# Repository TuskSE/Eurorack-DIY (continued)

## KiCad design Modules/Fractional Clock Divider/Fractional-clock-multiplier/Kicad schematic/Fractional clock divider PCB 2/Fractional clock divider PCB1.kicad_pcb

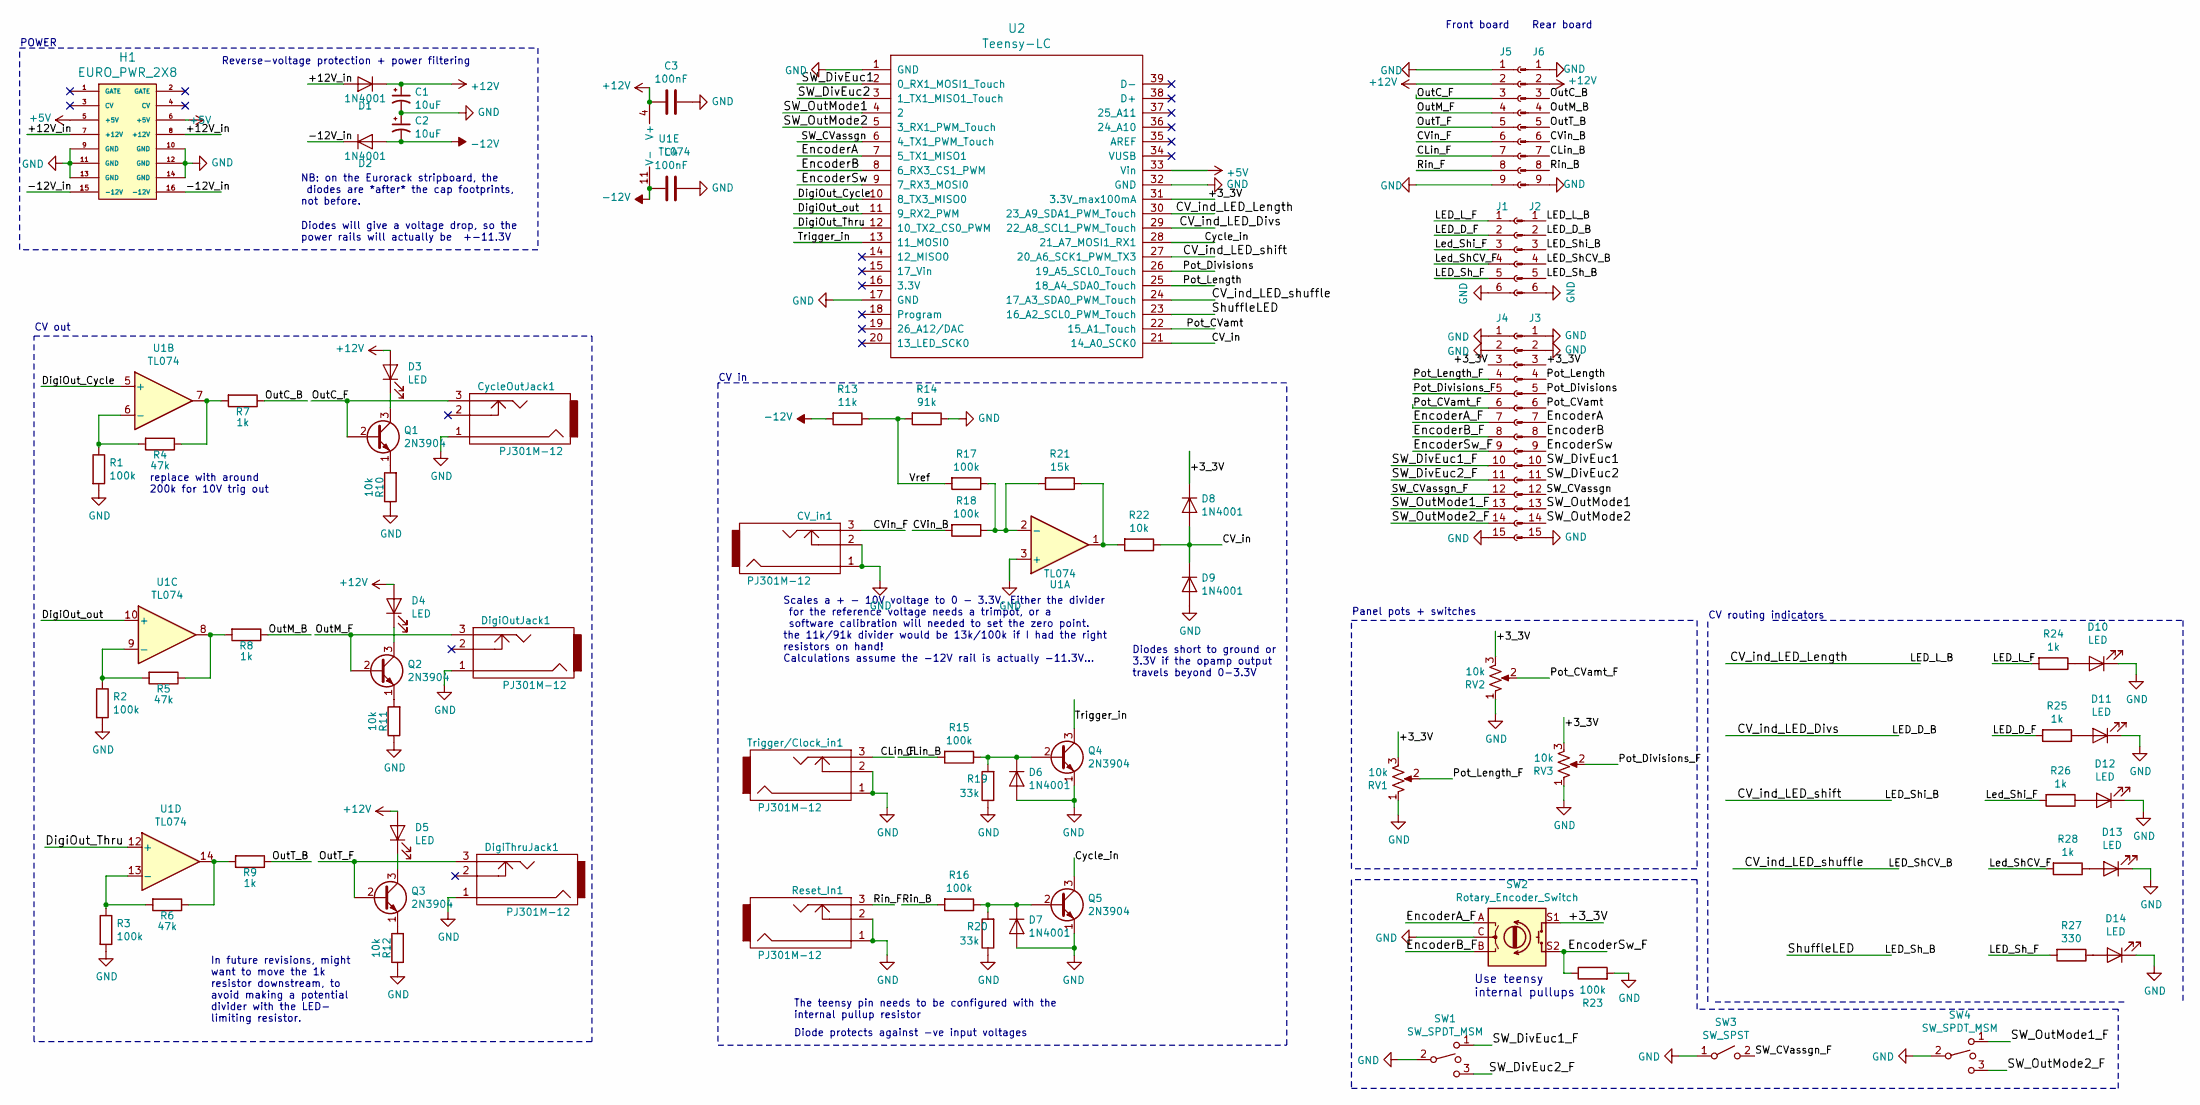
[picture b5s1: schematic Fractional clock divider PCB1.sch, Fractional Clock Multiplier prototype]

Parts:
C1, C2: 10uF; CP_Radial_D5.0mm_P2.00mm
C3, C4: 100nF; C_Rect_L11.5mm_W4.0mm_P10.00mm_MKT
CV_in1: PJ301M-12
CycleOutJack1: PJ301M-12
D1, D2, D6, D7, D8, D9: 1N4001; D_DO-41_SOD81_P10.16mm_Horizontal
D3, D4, D5, D10, D11, D12, D13, D14: LED; LED_D3.0mm
DigiOutJack1: PJ301M-12
DigiThruJack1: PJ301M-12
H1: EURO_PWR_2X8; PinSocket_2x08_P2.54mm_Vertical
J1: Conn_01x06_Female; PinHeader_1x06_P2.54mm_Vertical
J2: Conn_01x06_Male; PinHeader_1x06_P2.54mm_Vertical
J3: Conn_01x15_Male; PinHeader_1x15_P2.54mm_Vertical
J4: Conn_01x15_Female; PinHeader_1x15_P2.54mm_Vertical
J5: Conn_01x09_Female; PinHeader_1x09_P2.54mm_Vertical
J6: Conn_01x09_Male; PinHeader_1x09_P2.54mm_Vertical
Q1, Q2, Q3, Q4, Q5: 2N3904; TO-92_Inline
R1, R2, R3, R15, R16, R17, R18, R23: 100k; R_Axial_DIN0207_L6.3mm_D2.5mm_P10.16mm_Horizontal
R4, R5, R6: 47k; R_Axial_DIN0207_L6.3mm_D2.5mm_P10.16mm_Horizontal
R7, R8, R9, R24, R25, R26, R28: 1k; R_Axial_DIN0207_L6.3mm_D2.5mm_P10.16mm_Horizontal
R10, R11, R12, R22: 10k; R_Axial_DIN0207_L6.3mm_D2.5mm_P10.16mm_Horizontal
R13: 11k; R_Axial_DIN0207_L6.3mm_D2.5mm_P10.16mm_Horizontal
R14: 91k; R_Axial_DIN0207_L6.3mm_D2.5mm_P10.16mm_Horizontal
R19, R20: 33k; R_Axial_DIN0207_L6.3mm_D2.5mm_P10.16mm_Horizontal
R21: 15k; R_Axial_DIN0207_L6.3mm_D2.5mm_P10.16mm_Horizontal
R27: 330; R_Axial_DIN0207_L6.3mm_D2.5mm_P10.16mm_Horizontal
RV1, RV2, RV3: 10k; Alpha9mmPot
Reset_In1: PJ301M-12
SW1, SW4: SW_SPDT_MSM; SPDT toggle on-off-on
SW2: Rotary_Encoder_Switch; RotaryEncoder_Alps_EC11E-Switch_Vertical_H20mm_CircularMoun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
SW3: SW_SPST; SPST momentary push PBS105
Trigger/Clock_in1: PJ301M-12
U1: TL074; DIP-14_W7.62mm_LongPads
U2: Teensy-LC; TeensyLC_fixed_pads

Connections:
+5V: H1.5 (+5V), H1.6 (+5V), U2.33 (Vin)
+12V: C1.1, C3.2, D1.1 (K), D3.2 (A), D4.2 (A), D5.2 (A), J5.2, J6.2, U1.4 (V+)
-12V: C2.2, C4.1, D2.2 (A), R13.2, U1.11 (V-)
/+3_3V: D8.1 (K), J3.3, J4.3, RV1.3, RV2.3, RV3.3, SW2.S1, U2.31 (3.3V_max100mA)
/+12V_in: D1.2 (A), H1.7 (+12V), H1.8 (+12V)
/-12V_in: D2.1 (K), H1.15 (-12V), H1.16 (-12V)
/CLin_B: J6.7, R15.2
/CLin_F: J5.7, Trigger/Clock_in1.3
/CV_in: D8.2 (A), D9.1 (K), R22.1, U2.21 (14_A0_SCK0)
/CV_ind_LED_Divs: J2.2, U2.29 (22_A8_SCL1_PWM_Touch)
/CV_ind_LED_Length: J2.1, U2.30 (23_A9_SDA1_PWM_Touch)
/CV_ind_LED_shift: J2.3, U2.27 (20_A6_SCK1_PWM_TX3)
/CV_ind_LED_shuffle: J2.4, U2.24 (17_A3_SDA0_PWM_Touch)
/CVin_B: J6.6, R18.2
/CVin_F: CV_in1.3, J5.6
/Cycle_in: Q5.3 (C), U2.28 (21_A7_MOSI1_RX1)
/DigiOut_Cycle: U1.5 (+), U2.10 (8_TX3_MISO0)
/DigiOut_Thru: U1.12 (+), U2.12 (10_TX2_CS0_PWM)
/DigiOut_out: U1.10 (+), U2.11 (9_RX2_PWM)
/EncoderA: J3.7, U2.7 (5_TX1_MISO1)
/EncoderA_F: J4.7, SW2.A
/EncoderB: J3.8, U2.8 (6_RX3_CS1_PWM)
/EncoderB_F: J4.8, SW2.B
/EncoderSw: J3.9, U2.9 (7_RX3_MOSI0)
/EncoderSw_F: J4.9, R23.1, SW2.S2
/LED_D_F: J1.2, R25.2
/LED_L_F: J1.1, R24.2
/LED_Sh_B: J2.5, U2.23 (16_A2_SCL0_PWM_Touch)
/LED_Sh_F: J1.5, R27.2
/Led_ShCV_F: J1.4, R28.2
/Led_Shi_F: J1.3, R26.2
/OutC_B: J6.3, R7.1
/OutC_F: CycleOutJack1.3, J5.3, Q1.2 (B)
/OutM_B: J6.4, R8.1
/OutM_F: DigiOutJack1.3, J5.4, Q2.2 (B)
/OutT_B: J6.5, R9.1
/OutT_F: DigiThruJack1.3, J5.5, Q3.2 (B)
/Pot_CVamt: J3.6, U2.22 (15_A1_Touch)
/Pot_CVamt_F: J4.6, RV2.2
/Pot_Divisions: J3.5, U2.26 (19_A5_SCL0_Touch)
/Pot_Divisions_F: J4.5, RV3.2
/Pot_Length: J3.4, U2.25 (18_A4_SDA0_Touch)
/Pot_Length_F: J4.4, RV1.2
/Rin_B: J6.8, R16.2
/Rin_F: J5.8, Reset_In1.3
/SW_CVassgn: J3.12, U2.6 (4_TX1_PWM_Touch)
/SW_CVassgn_F: J4.12, SW3.2 (B)
/SW_DivEuc1: J3.10, U2.2 (0_RX1_MOSI1_Touch)
/SW_DivEuc1_F: J4.10, SW1.1
/SW_DivEuc2: J3.11, U2.3 (1_TX1_MISO1_Touch)
/SW_DivEuc2_F: J4.11, SW1.3
/SW_OutMode1: J3.13, U2.4 (2)
/SW_OutMode1_F: J4.13, SW4.1
/SW_OutMode2: J3.14, U2.5 (3_RX1_PWM_Touch)
/SW_OutMode2_F: J4.14, SW4.3
/Trigger_in: Q4.3 (C), U2.13 (11_MOSI0)
/Vref: R13.1, R14.2, R17.2
GND: C1.2, C2.1, C3.1, C4.2, CV_in1.1, CV_in1.2, CycleOutJack1.1, D6.2 (A), D7.2 (A), D9.2 (A), D10.1 (K), D11.1 (K), D12.1 (K), D13.1 (K), D14.1 (K), DigiOutJack1.1, DigiThruJack1.1, H1.9 (GND), H1.10 (GND), H1.11 (GND), H1.12 (GND), H1.13 (GND), H1.14 (GND), J1.6, J2.6, J3.1, J3.2, J3.15, J4.1, J4.2, J4.15, J5.1, J5.9, J6.1, J6.9, Q4.1 (E), Q5.1 (E), R1.2, R2.2, R3.2, R10.1, R11.1, R12.1, R14.1, R19.1, R20.1, R23.2, RV1.1, RV2.1, RV3.1, Reset_In1.1, Reset_In1.2, SW1.2, SW2.C, SW3.1 (A), SW4.2, Trigger/Clock_in1.1, Trigger/Clock_in1.2, U1.3 (+), U2.1 (GND), U2.17 (GND), U2.32 (GND)
unnamed: D3.1 (K), Q1.3 (C)
unnamed: D4.1 (K), Q2.3 (C)
unnamed: D5.1 (K), Q3.3 (C)
unnamed: D6.1 (K), Q4.2 (B), R15.1, R19.2
unnamed: D7.1 (K), Q5.2 (B), R16.1, R20.2
unnamed: D10.2 (A), R24.1
unnamed: D11.2 (A), R25.1
unnamed: D12.2 (A), R26.1
unnamed: D13.2 (A), R28.1
unnamed: D14.2 (A), R27.1
unnamed: Q1.1 (E), R10.2
unnamed: Q2.1 (E), R11.2
unnamed: Q3.1 (E), R12.2
unnamed: R1.1, R4.2, U1.6 (-)
unnamed: R2.1, R5.2, U1.9 (-)
unnamed: R3.1, R6.2, U1.13 (-)
unnamed: R4.1, R7.2, U1.7
unnamed: R5.1, R8.2, U1.8
unnamed: R6.1, R9.2, U1.14
unnamed: R17.1, R18.1, R21.2, U1.2 (-)
unnamed: R21.1, R22.2, U1.1

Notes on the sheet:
NB: on the Eurorack stripboard, the diodes are *after* the cap footprints, not before.
Diodes will give a voltage drop, so the power rails will actually be ~ +-11.3V
Reverse-voltage protection + power filtering
Scales a + - 10V voltage to 0 - 3.3V. Either the divider for the reference voltage needs a trimpot, or a software calibration will needed to set the zero point. the 11k/91k divider would be 13k/100k if I had the right resistors on hand! Calculations assume the -12V rail is actually -11.3V...
Diodes short to ground or 3.3V if the opamp output travels beyond 0-3.3V
Use teensy internal pullups
In future revisions, might want to move the 1k resistor downstream, to avoid making a potential divider with the LED- limiting resistor.
The teensy pin needs to be configured with the internal pullup resistor
Diode protects against -ve input voltages
Front board
Rear board
POWER
CV out
CV in
CV routing indicators
Panel pots + switches
replace with around 200k for 10V trig out

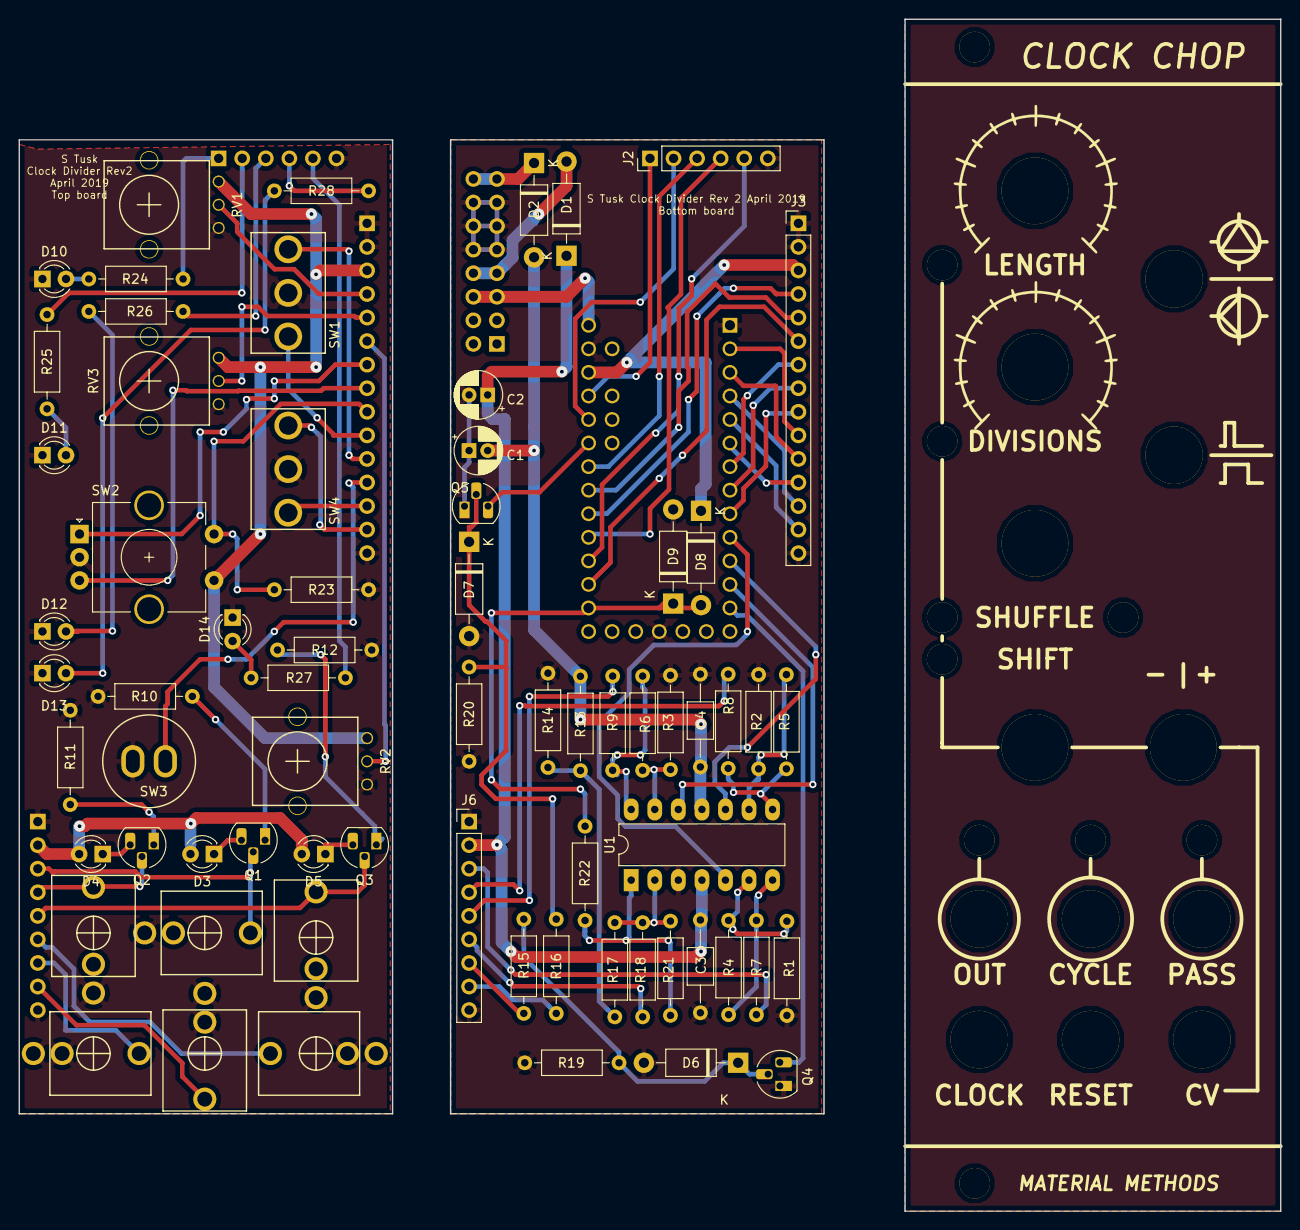
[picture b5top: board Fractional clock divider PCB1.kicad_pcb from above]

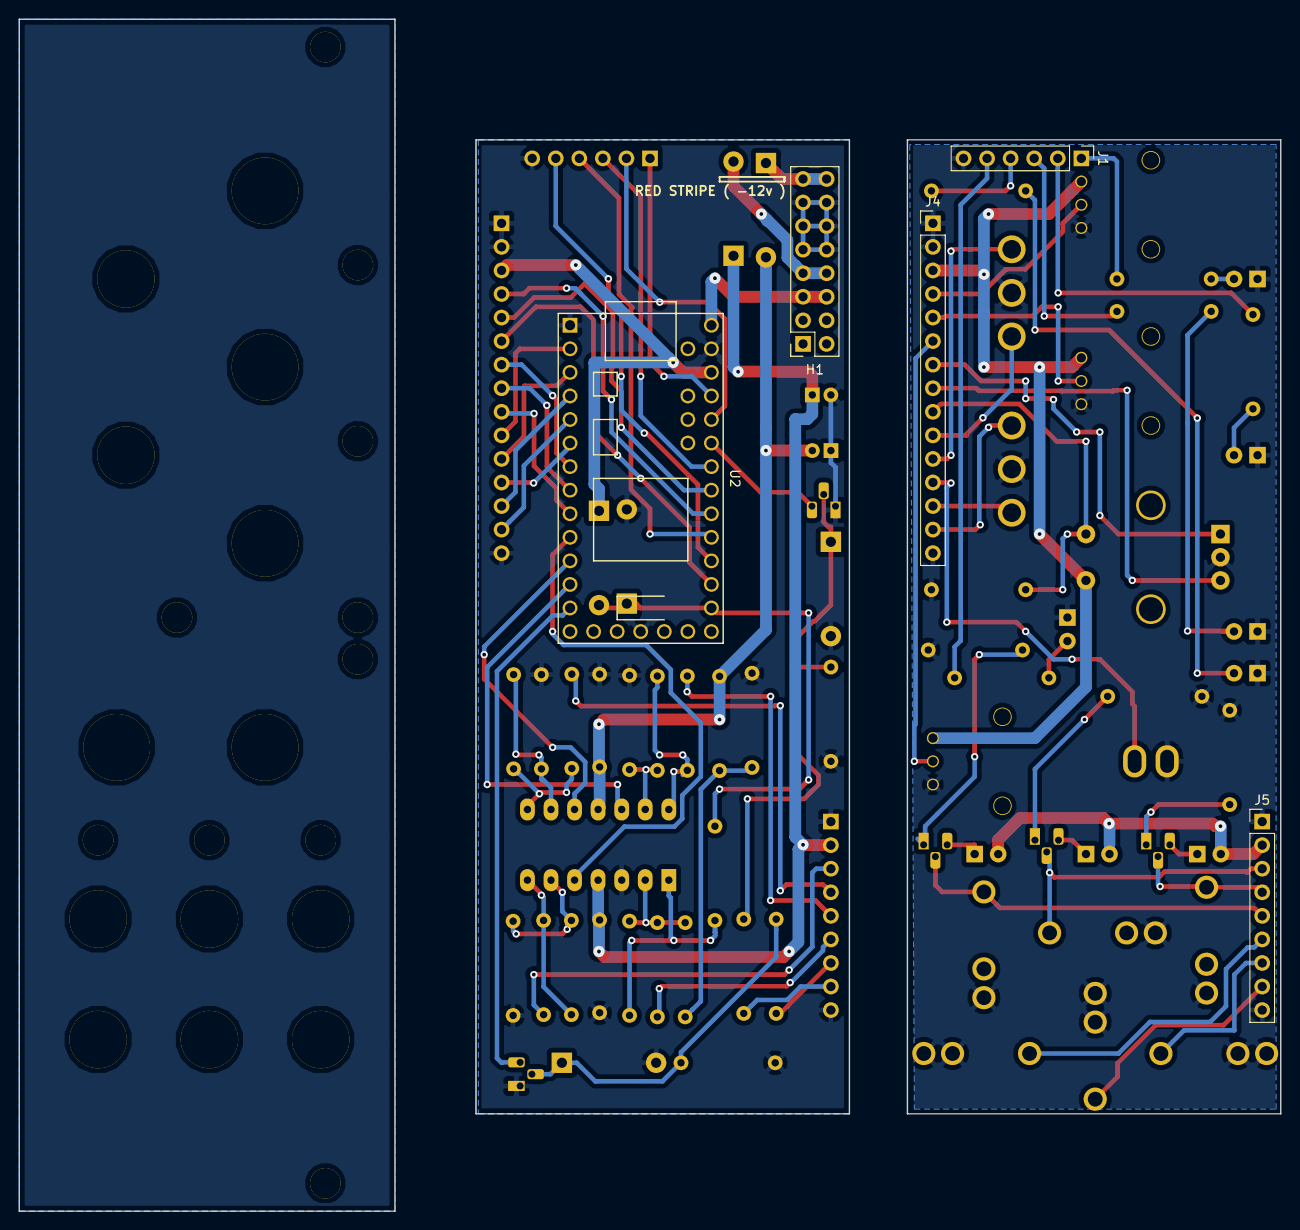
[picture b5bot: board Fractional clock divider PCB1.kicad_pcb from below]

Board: 2 copper layers, 136.0 x 128.5 mm, 73 parts (5 on the bottom side), 79 nets.

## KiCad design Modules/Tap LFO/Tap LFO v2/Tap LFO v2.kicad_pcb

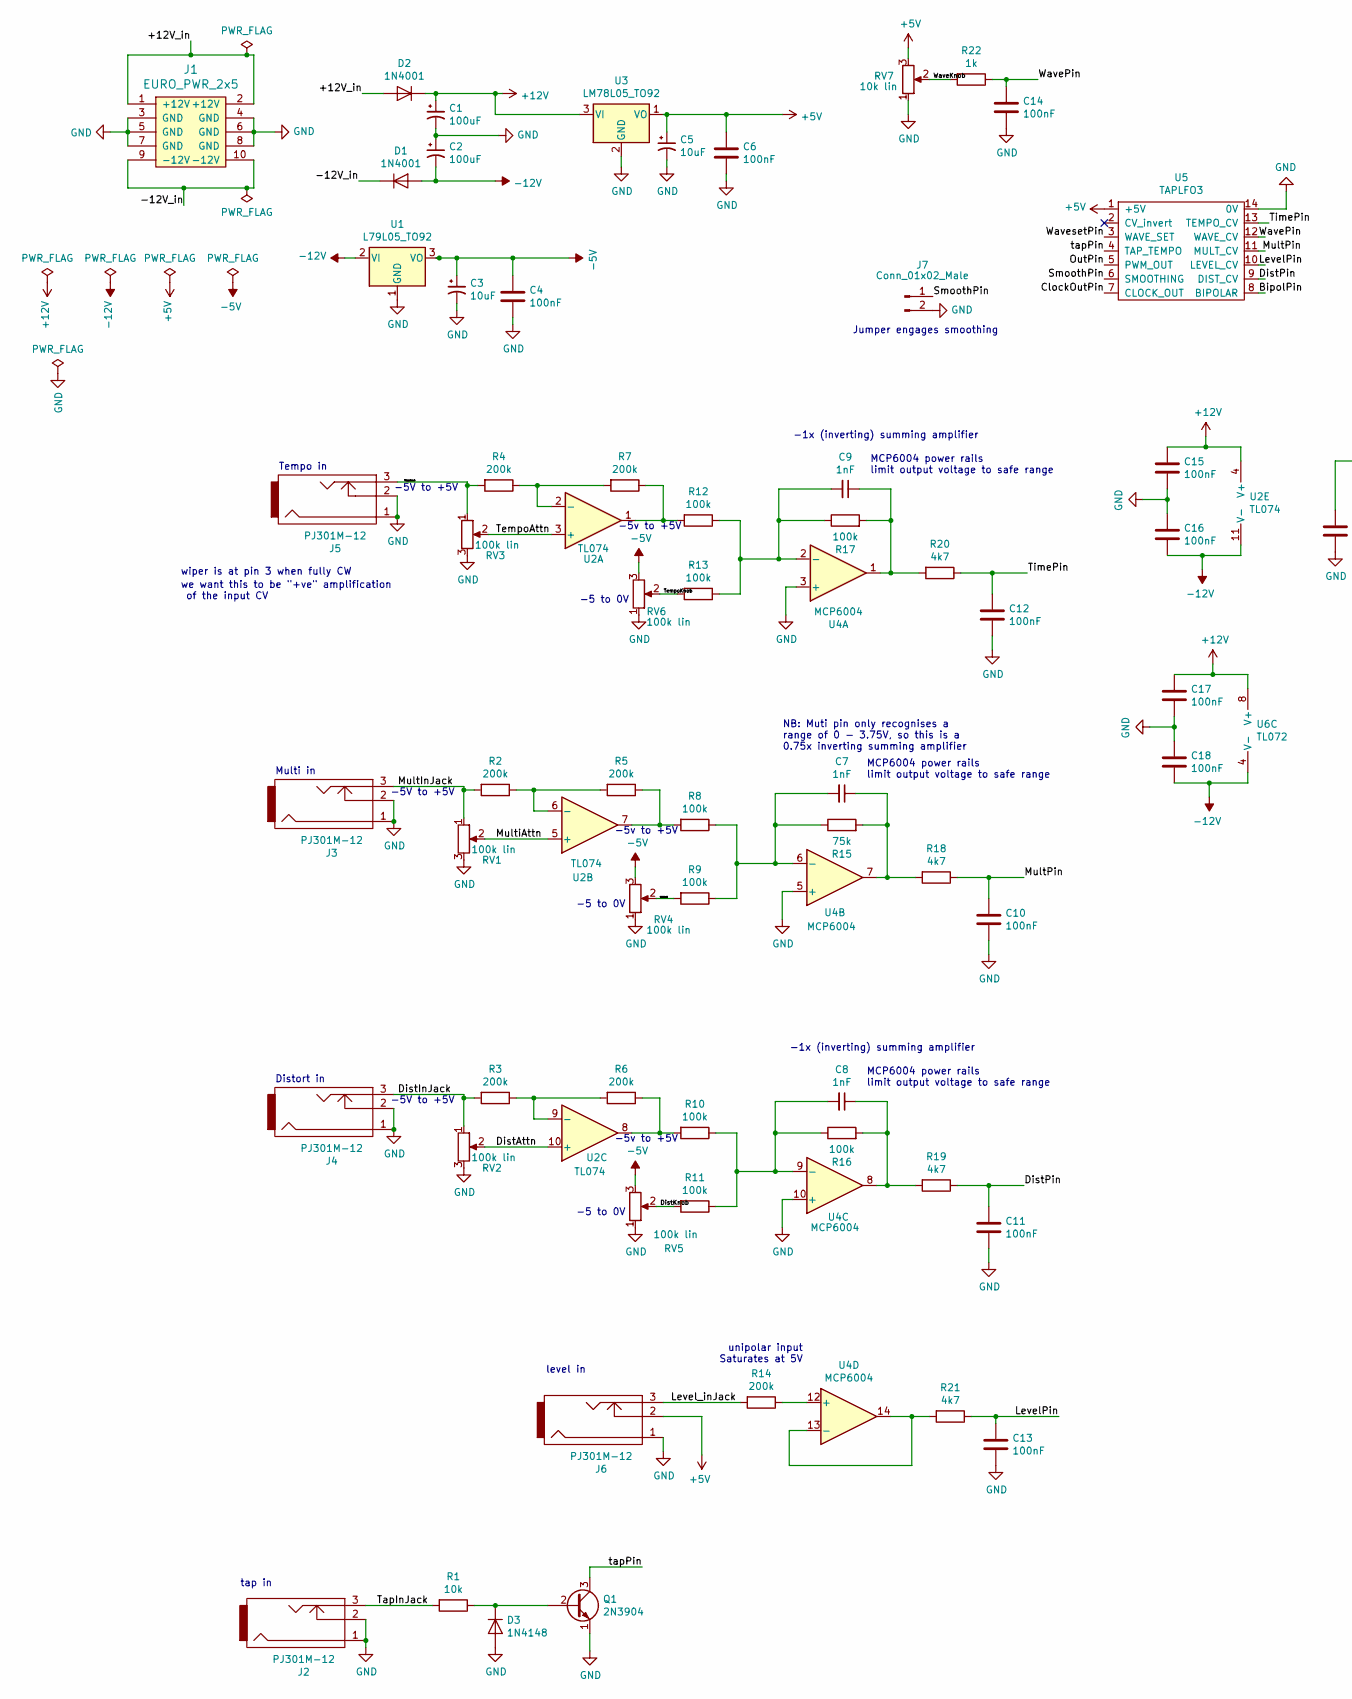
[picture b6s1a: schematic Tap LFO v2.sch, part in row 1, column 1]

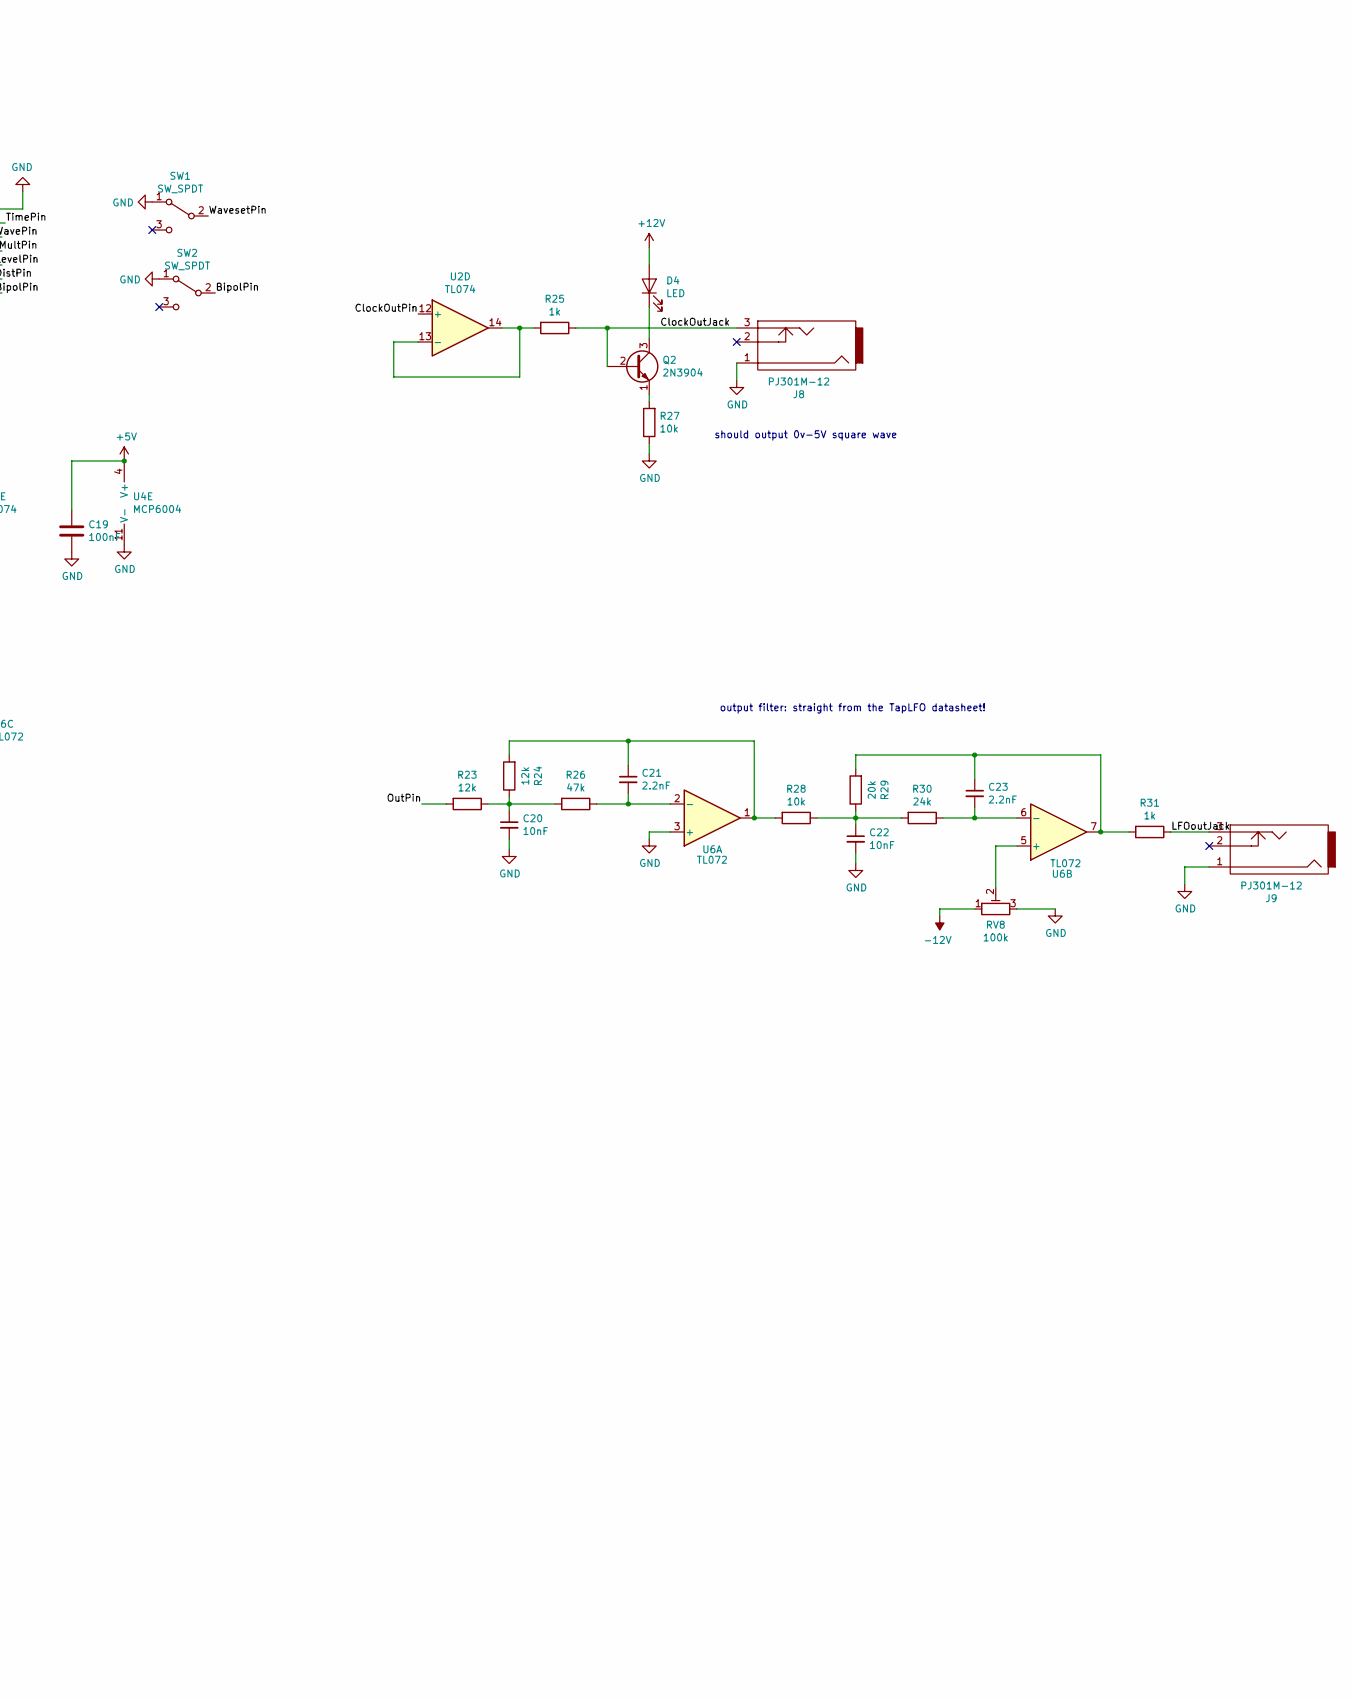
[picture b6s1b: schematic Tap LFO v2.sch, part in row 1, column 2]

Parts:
C1, C2: 100uF; CP_Radial_D6.3mm_P2.50mm
C3, C5: 10uF; CP_Radial_D5.0mm_P2.00mm
C4, C6, C10, C11, C12, C13, C14, C15, C16, C17, C18, C19: 100nF; C_0805_2012Metric_Pad1.15x1.40mm_HandSolder
C7, C8, C9: 1nF; C_0805_2012Metric_Pad1.15x1.40mm_HandSolder
C20, C22: 10nF; C_0805_2012Metric_Pad1.15x1.40mm_HandSolder
C21, C23: 2.2nF; C_0805_2012Metric_Pad1.15x1.40mm_HandSolder
D1, D2: 1N4001; D_DO-41_SOD81_P3.81mm_Vertical_AnodeUp
D3: 1N4148; D_DO-35_SOD27_P3.81mm_Vertical_AnodeUp
D4: LED; LED3mm
J1: EURO_PWR_2x5; IDC-Header_2x05_P2.54mm_Vertical
J2, J3, J4, J5, J6, J8, J9: PJ301M-12; PJ301M-12-MoreMetal
J7: Conn_01x02_Male; PinHeader_1x02_P2.54mm_Vertical
Q1, Q2: 2N3904; TO-92_Inline
R1, R27, R28: 10k; R_0805_2012Metric_Pad1.15x1.40mm_HandSolder
R2, R3, R4, R5, R6, R7, R14: 200k; R_0805_2012Metric_Pad1.15x1.40mm_HandSolder
R8, R9, R10, R11, R12, R13, R16, R17: 100k; R_0805_2012Metric_Pad1.15x1.40mm_HandSolder
R15: 75k; R_0805_2012Metric_Pad1.15x1.40mm_HandSolder
R18, R19, R20, R21: 4k7; R_0805_2012Metric_Pad1.15x1.40mm_HandSolder
R22, R25, R31: 1k; R_0805_2012Metric_Pad1.15x1.40mm_HandSolder
R23, R24: 12k; R_0805_2012Metric_Pad1.15x1.40mm_HandSolder
R26: 47k; R_0805_2012Metric_Pad1.15x1.40mm_HandSolder
R29: 20k; R_0805_2012Metric_Pad1.15x1.40mm_HandSolder
R30: 24k; R_0805_2012Metric_Pad1.15x1.40mm_HandSolder
RV1, RV2, RV3, RV4, RV5, RV6: 100k lin; Alpha9mmPot
RV7: 10k lin; Alpha9mmPot
RV8: 100k; Potentiometer_Runtron_RM-065_Vertical
SW1, SW2: SW_SPDT; SPDT toggle on-off-on
U1: L79L05_TO92; TO-92_Inline
U2: TL074; SOIC-14_3.9x8.7mm_P1.27mm
U3: LM78L05_TO92; TO-92_Inline
U4: MCP6004; SOIC-14_3.9x8.7mm_P1.27mm
U5: TAPLFO3; DIP-14_W7.62mm_Socket_LongPads
U6: TL072; SOIC-8_3.9x4.9mm_P1.27mm

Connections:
+5V: C5.1, C6.1, C19.1, J6.2, RV7.3, U3.1 (VO), U4.4 (V+), U5.1 (+5V)
+12V: C1.1, C15.1, C17.1, D2.1 (K), D4.2 (A), U2.4 (V+), U3.3 (VI), U6.8 (V+)
-5V: C3.1, C4.1, RV4.3, RV5.3, RV6.3, U1.3 (VO)
-12V: C2.2, C16.2, C18.2, D1.2 (A), RV8.1, U1.2 (VI), U2.11 (V-), U6.4 (V-)
/+12V_in: D2.2 (A), J1.1 (+12V), J1.2 (+12V)
/-12V_in: D1.1 (K), J1.9 (-12V), J1.10 (-12V)
/BipolPin: SW2.2 (B), U5.8 (BIPOLAR)
/ClockOutJack: J8.3, Q2.2 (B), R25.1
/ClockOutPin: U2.12 (+), U5.7 (CLOCK_OUT)
/DistAttn: RV2.2, U2.10 (+)
/DistInJack: J4.3, R3.2, RV2.1
/DistKnob: R11.2, RV5.2
/DistPin: C11.1, R19.1, U5.9 (DIST_CV)
/LFOoutJack: J9.3, R31.1
/LevelPin: C13.1, R21.1, U5.10 (LEVEL_CV)
/Level_inJack: J6.3, R14.2
/MultInJack: J3.3, R2.2, RV1.1
/MultKnob: R9.2, RV4.2
/MultPin: C10.1, R18.1, U5.11 (MULT_CV)
/MultiAttn: RV1.2, U2.5 (+)
/OutPin: R23.2, U5.5 (PWM_OUT)
/SmoothPin: J7.1, U5.6 (SMOOTHING)
/TapInJack: J2.3, R1.2
/TempoAttn: RV3.2, U2.3 (+)
/TempoInJack: J5.3, R4.2, RV3.1
/TempoKnob: R13.2, RV6.2
/TimePin: C12.1, R20.1, U5.13 (TEMPO_CV)
/WaveKnob: R22.2, RV7.2
/WavePin: C14.1, R22.1, U5.12 (WAVE_CV)
/WavesetPin: SW1.2 (B), U5.3 (WAVE_SET)
/tapPin: Q1.3 (C), U5.4 (TAP_TEMPO)
GND: C1.2, C2.1, C3.2, C4.2, C5.2, C6.2, C10.2, C11.2, C12.2, C13.2, C14.2, C15.2, C16.1, C17.2, C18.1, C19.2, C20.2, C22.2, D3.2 (A), J1.3 (GND), J1.4 (GND), J1.5 (GND), J1.6 (GND), J1.7 (GND), J1.8 (GND), J2.1, J2.2, J3.1, J3.2, J4.1, J4.2, J5.1, J5.2, J6.1, J7.2, J8.1, J9.1, Q1.1 (E), R27.1, RV1.3, RV2.3, RV3.3, RV4.1, RV5.1, RV6.1, RV7.1, RV8.3, SW1.1 (A), SW2.1 (A), U1.1 (GND), U3.2 (GND), U4.3 (+), U4.5 (+), U4.10 (+), U4.11 (V-), U5.14 (0V), U6.3 (+)
unnamed: C7.1, R15.2, R18.2, U4.7
unnamed: C7.2, R8.1, R9.1, R15.1, U4.6 (-)
unnamed: C8.1, R16.2, R19.2, U4.8
unnamed: C8.2, R10.1, R11.1, R16.1, U4.9 (-)
unnamed: C9.1, R17.2, R20.2, U4.1
unnamed: C9.2, R12.1, R13.1, R17.1, U4.2 (-)
unnamed: C21.1, R24.2, R28.2, U6.1
unnamed: C21.2, R26.1, U6.2 (-)
unnamed: C23.1, R29.2, R31.2, U6.7
unnamed: C23.2, R30.1, U6.6 (-)
unnamed: D3.1 (K), Q1.2 (B), R1.1
unnamed: D4.1 (K), Q2.3 (C)
unnamed: Q2.1 (E), R27.2
unnamed: R2.1, R5.2, U2.6 (-)
unnamed: R3.1, R6.2, U2.9 (-)
unnamed: R4.1, R7.2, U2.2 (-)
unnamed: R5.1, R8.2, U2.7
unnamed: R6.1, R10.2, U2.8
unnamed: R7.1, R12.2, U2.1
unnamed: R14.1, U4.12 (+)
unnamed: R21.2, U4.13 (-), U4.14
unnamed: R25.2, U2.13 (-), U2.14
unnamed: RV8.2, U6.5 (+)

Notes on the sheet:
Jumper engages smoothing
should output 0v-5V square wave
level in
unipolar input Saturates at 5V
-5V to +5V
-5v to +5V
Tempo in
-5 to 0V
-1x (inverting) summing amplifier
MCP6004 power rails limit output voltage to safe range
Multi in
Distort in
NB: Muti pin only recognises a range of 0 - 3.75V, so this is a 0.75x inverting summing amplifier
tap in
output filter: straight from the TapLFO datasheet!
wiper is at pin 3 when fully CW
we want this to be "+ve" amplification of the input CV

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
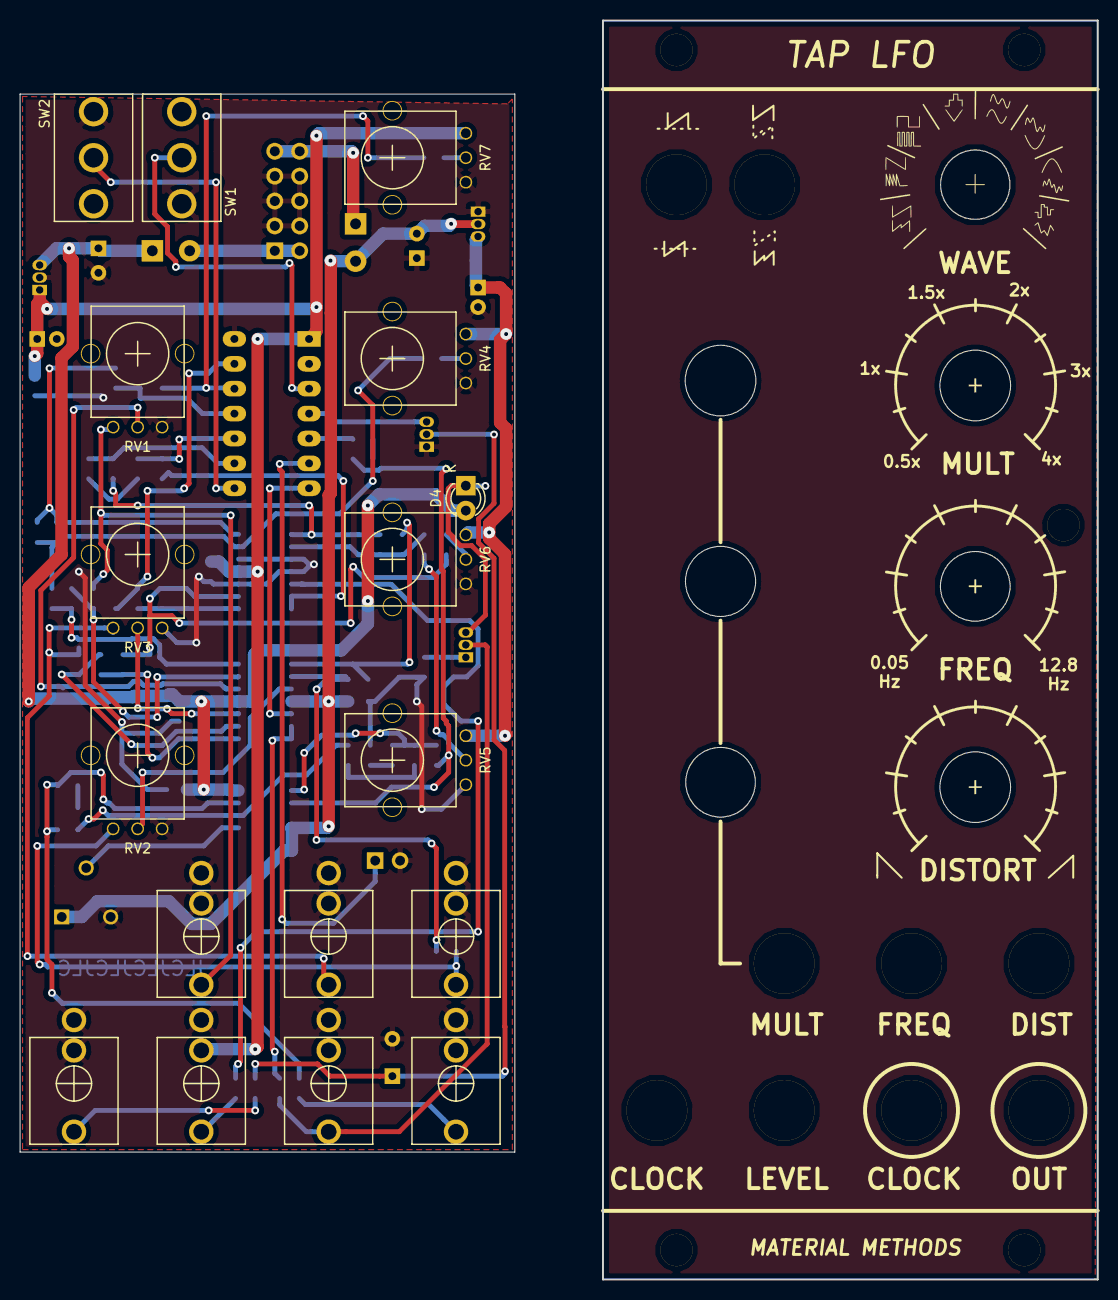
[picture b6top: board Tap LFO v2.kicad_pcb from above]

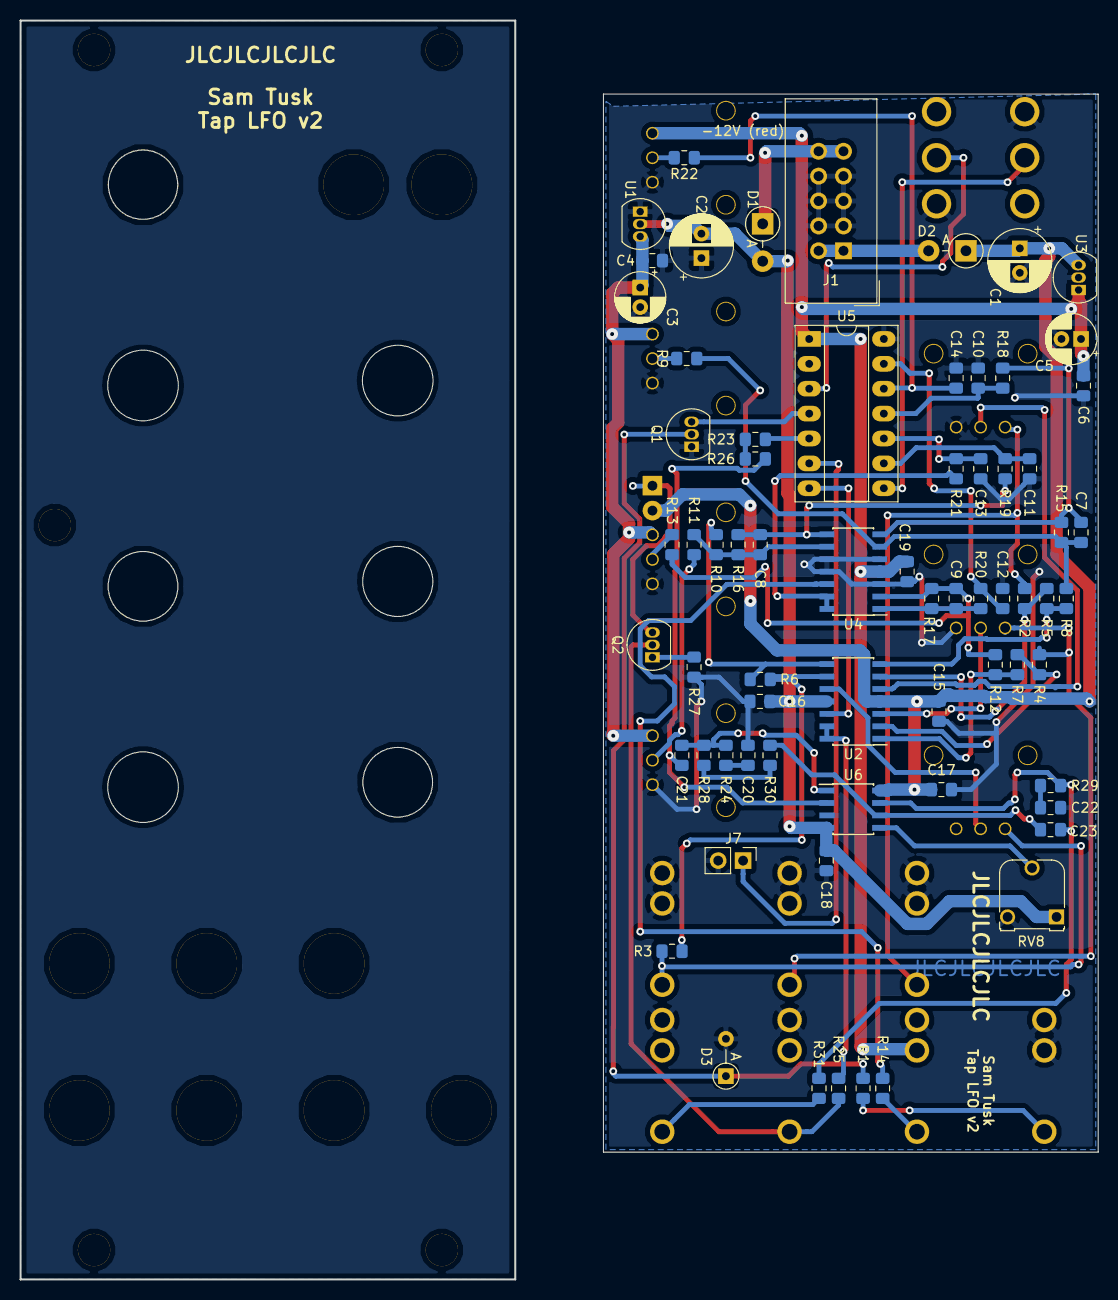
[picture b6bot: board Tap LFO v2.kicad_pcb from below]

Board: 2 copper layers, 50.5 x 108.0 mm, 85 parts (68 on the bottom side), 59 nets.
